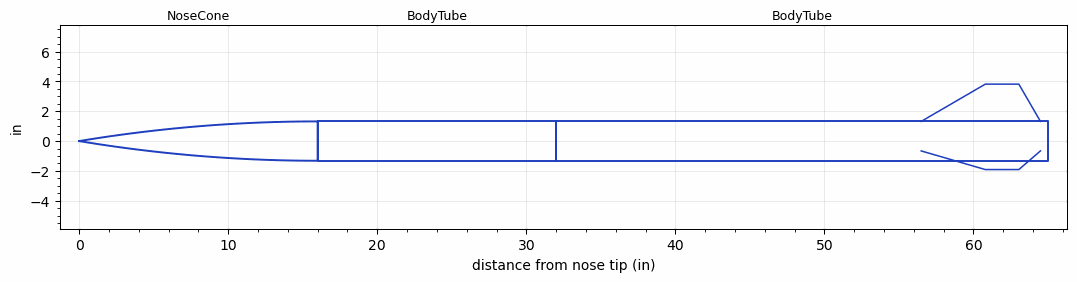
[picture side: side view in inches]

<RASAeroDocument>
 <FileVersion>2</FileVersion>
 <RocketDesign>
  <NoseCone>
   <Length>16</Length>
   <Diameter>2.64</Diameter>
   <Shape>Tangent Ogive</Shape>
   <Location>0</Location>
  </NoseCone>
  <BodyTube>
   <Length>16</Length>
   <Diameter>2.64</Diameter>
   <Location>16</Location>
  </BodyTube>
  <BodyTube>
   <Length>32.9921</Length>
   <Diameter>2.64</Diameter>
   <Location>32</Location>
   <Fin>
    <Count>3</Count>
    <Chord>8</Chord>
    <Span>2.5</Span>
    <SweepDistance>4.3</SweepDistance>
    <TipChord>2.25</TipChord>
    <Thickness>0.118</Thickness>
    <Location>8.5</Location>
    <AirfoilSection>Square</AirfoilSection>
   </Fin>
  </BodyTube>
  <Surface>Camouflage Paint</Surface>
  <ModifiedBarrowman>False</ModifiedBarrowman>
  <Turbulence>False</Turbulence>
  <UseBooster1>False</UseBooster1>
  <UseBooster2>False</UseBooster2>
 </RocketDesign>
 <LaunchSite>
  <Altitude>0</Altitude>
  <Pressure>29.92</Pressure>
  <RodAngle>0</RodAngle>
  <RodLength>59.06</RodLength>
  <Temperature>59</Temperature>
  <WindSpeed>4.47</WindSpeed>
 </LaunchSite>
 <Recovery>
  <Altitude1>656.168</Altitude1>
  <Altitude2>656.168</Altitude2>
  <DeviceType1>Parachute</DeviceType1>
  <DeviceType2>Parachute</DeviceType2>
  <Event1>True</Event1>
  <Event2>True</Event2>
  <Size1>29.5275</Size1>
  <Size2>15.748</Size2>
  <EventType1>Altitude</EventType1>
  <EventType2>Apogee</EventType2>
  <CD1>0.75</CD1>
  <CD2>0</CD2>
 </Recovery>
 <SimulationList>
  <Simulation>
   <SustainerLaunchWt>4.8325</SustainerLaunchWt>
   <SustainerCG>40.3482</SustainerCG>
   <SustainerIgnitionDelay>0</SustainerIgnitionDelay>
   <Booster1SeparationDelay>0</Booster1SeparationDelay>
   <Booster1IgnitionDelay>0</Booster1IgnitionDelay>
   <IncludeBooster1>False</IncludeBooster1>
   <Booster2Delay>0</Booster2Delay>
   <IncludeBooster2>False</IncludeBooster2>
  </Simulation>
  <Simulation>
   <SustainerLaunchWt>6.7898</SustainerLaunchWt>
   <SustainerCG>45.5189</SustainerCG>
   <SustainerIgnitionDelay>0</SustainerIgnitionDelay>
   <Booster1SeparationDelay>0</Booster1SeparationDelay>
   <Booster1IgnitionDelay>0</Booster1IgnitionDelay>
   <IncludeBooster1>False</IncludeBooster1>
   <Booster2Delay>0</Booster2Delay>
   <IncludeBooster2>False</IncludeBooster2>
  </Simulation>
  <Simulation>
   <SustainerLaunchWt>5.4119</SustainerLaunchWt>
   <SustainerCG>41.8831</SustainerCG>
   <SustainerIgnitionDelay>0</SustainerIgnitionDelay>
   <Booster1SeparationDelay>0</Booster1SeparationDelay>
   <Booster1IgnitionDelay>0</Booster1IgnitionDelay>
   <IncludeBooster1>False</IncludeBooster1>
   <Booster2Delay>0</Booster2Delay>
   <IncludeBooster2>False</IncludeBooster2>
  </Simulation>
  <Simulation>
   <SustainerLaunchWt>5.5116</SustainerLaunchWt>
   <SustainerCG>41.8387</SustainerCG>
   <SustainerIgnitionDelay>0</SustainerIgnitionDelay>
   <Booster1SeparationDelay>0</Booster1SeparationDelay>
   <Booster1IgnitionDelay>0</Booster1IgnitionDelay>
   <IncludeBooster1>False</IncludeBooster1>
   <Booster2Delay>0</Booster2Delay>
   <IncludeBooster2>False</IncludeBooster2>
  </Simulation>
  <Simulation>
   <SustainerLaunchWt>4.9328</SustainerLaunchWt>
   <SustainerCG>40.7614</SustainerCG>
   <SustainerIgnitionDelay>0</SustainerIgnitionDelay>
   <Booster1SeparationDelay>0</Booster1SeparationDelay>
   <Booster1IgnitionDelay>0</Booster1IgnitionDelay>
   <IncludeBooster1>False</IncludeBooster1>
   <Booster2Delay>0</Booster2Delay>
   <IncludeBooster2>False</IncludeBooster2>
  </Simulation>
  <Simulation>
   <SustainerLaunchWt>4.8502</SustainerLaunchWt>
   <SustainerCG>40.4364</SustainerCG>
   <SustainerIgnitionDelay>0</SustainerIgnitionDelay>
   <Booster1SeparationDelay>0</Booster1SeparationDelay>
   <Booster1IgnitionDelay>0</Booster1IgnitionDelay>
   <IncludeBooster1>False</IncludeBooster1>
   <Booster2Delay>0</Booster2Delay>
   <IncludeBooster2>False</IncludeBooster2>
  </Simulation>
 </SimulationList>
</RASAeroDocument>
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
